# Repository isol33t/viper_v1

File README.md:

# Duck Viper v1 PCB

This repository contains KiCad files for an attempt at the Duck Viper v1 PCB design.

- Work In Progress
- Optional Split Shifts, Split Backspace, Stepped Caps Lock & ISO Enter
- No LEDs
- With 5 rows and 14 columns, there is only 1 pin left on the Atmega

## Files Included
- KiCad project files
- Schematic
- PCB layout

## Usage
Open the project in KiCad to view and modify the design.

## Revision 5.2025

## Thanks yo
- https://github.com/ruiqimao/keyboard-pcb-guide
- https://wiki.ai03.com/books/pcb-design
- https://github.com/evyd13/plain60-b
- https://github.com/evyd13/plain60-c
- https://www.masterzen.fr/2020/05/03/designing-a-keyboard-part-1/
- https://imgur.com/LQXco3J

## Todo
- Leds?
- https://github.com/adamws/keyboard-tools
- https://keyboard-tools.xyz

## Notes
- Is the reset switch position correct?
- [Japanese duplex matrix](https://kbd.news/The-Japanese-duplex-matrix-1391.html)
- [Pulldown resistor on KMAC Happy](https://geekhack.org/index.php?topic=87703.msg2485259#msg2485259)
- [Nexperia 74HC237 3-to-8 line decoder, demultiplexer with address latches](https://assets.nexperia.com/documents/data-sheet/74HC237.pdf)
- [hasu re: 74HC238](https://geekhack.org/index.php?topic=35065.msg966423#msg966423)

## License
MIT License

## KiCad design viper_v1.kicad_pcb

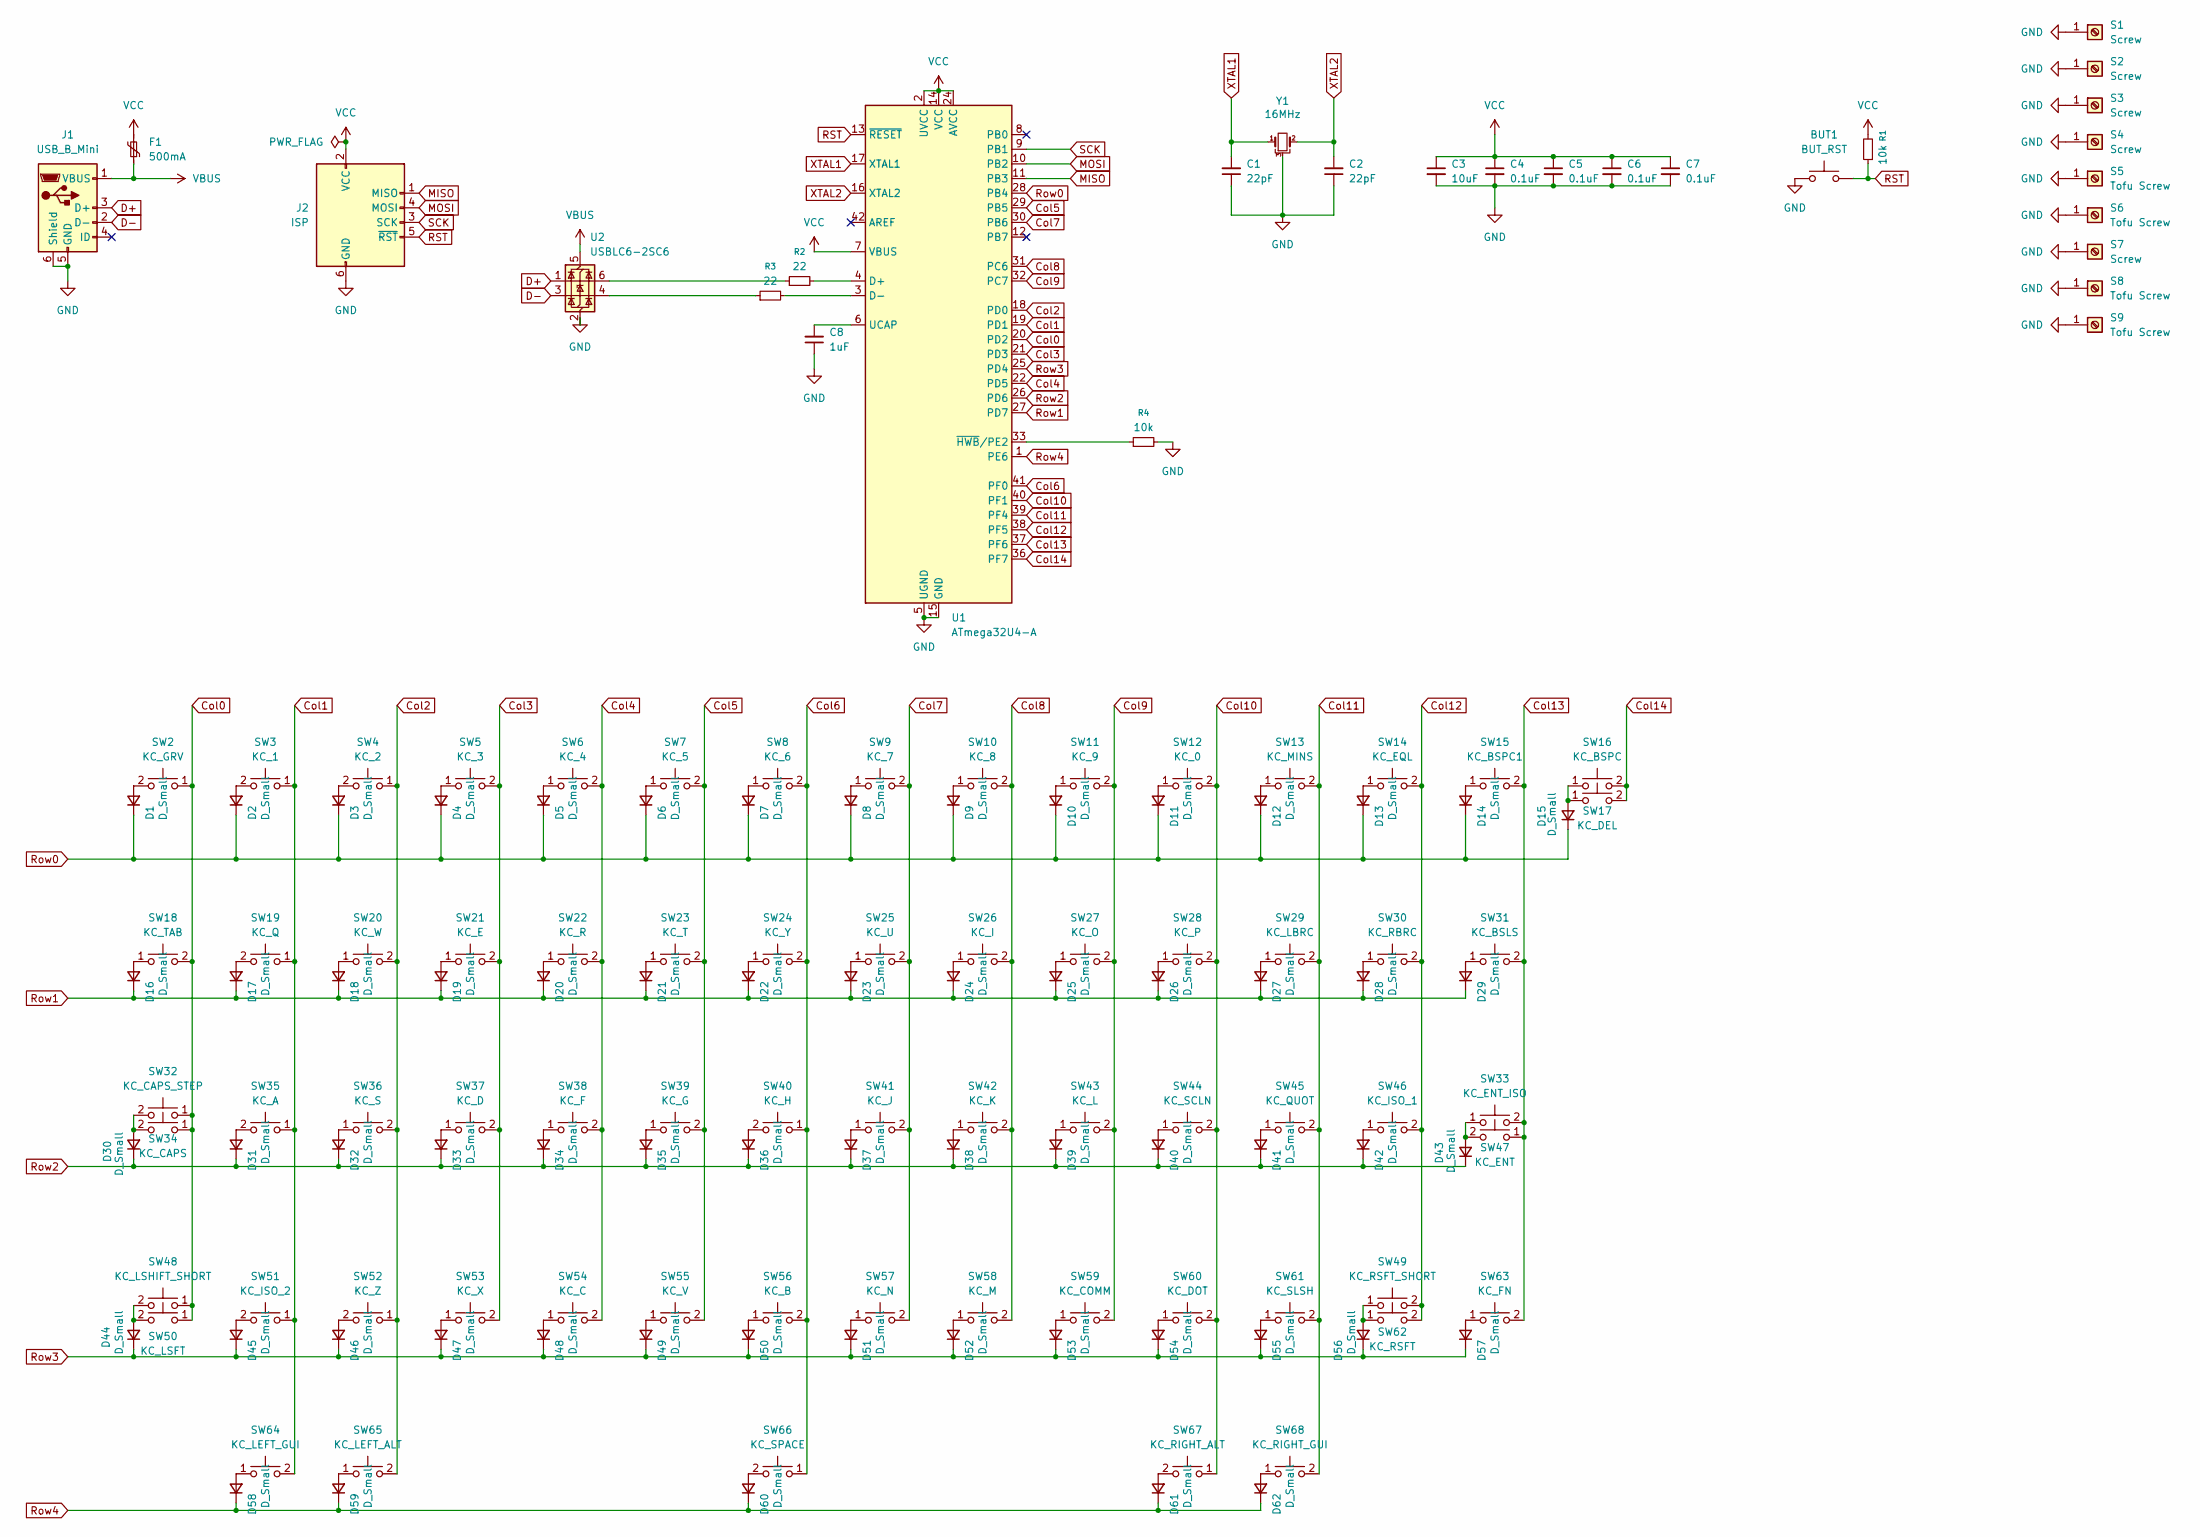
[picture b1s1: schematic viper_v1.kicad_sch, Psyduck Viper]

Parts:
BUT1: BUT_RST; SW_SPST_TL3342
C1, C2: 22pF; C_0805_2012Metric
C3: 10uF; C_0805_2012Metric
C4, C5, C6, C7: 0.1uF; C_0805_2012Metric
C8: 1uF; C_0805_2012Metric
D1, D2, D3, D4, D5, D6, D7, D8, D9, D10, D11, D12, D13, D14, D15, D16, D17, D18, D19, D20, D21, D22, D23, D24, D25, D26, D27, D28, D29, D30, D31, D32, D33, D34, D35, D36, D37, D38, D39, D40, D41, D42, D43, D44, D45, D46, D47, D48, D49, D50, D51, D52, D53, D54, D55, D56, D57, D58, D59, D60, D61, D62: D_Small; D_0805_2012Metric
F1: 500mA; Fuse_0805_2012Metric
J1: USB_B_Mini; HRO-U-M-M5DD-W-1
J2: ISP; isp_standard
R1, R4: 10k; R_0805_2012Metric
R2, R3: 22; R_0805_2012Metric
S1, S2, S3, S4, S7: Screw; 5.5_5x2.5mm
S5, S6, S8, S9: Tofu Screw; 10x5_7x2.5mm
SW2: KC_GRV; MX-Solderable-1U
SW3: KC_1; MX-Solderable-1U
SW4: KC_2; MX-Solderable-1U
SW5: KC_3; MX-Solderable-1U
SW6: KC_4; MX-Solderable-1U
SW7: KC_5; MX-Solderable-1U
SW8: KC_6; MX-Solderable-1U
SW9: KC_7; MX-Solderable-1U
SW10: KC_8; MX-Solderable-1U
SW11: KC_9; MX-Solderable-1U
SW12: KC_0; MX-Solderable-1U
SW13: KC_MINS; MX-Solderable-1U
SW14: KC_EQL; MX-Solderable-1U
SW15: KC_BSPC1; MX-Solderable-1U
SW16: KC_BSPC; MX-Solderable-2U
SW17: KC_DEL; MX-Solderable-1U
SW18: KC_TAB; MX-Solderable-1.5U
SW19: KC_Q; MX-Solderable-1U
SW20: KC_W; MX-Solderable-1U
SW21: KC_E; MX-Solderable-1U
SW22: KC_R; MX-Solderable-1U
SW23: KC_T; MX-Solderable-1U
SW24: KC_Y; MX-Solderable-1U
SW25: KC_U; MX-Solderable-1U
SW26: KC_I; MX-Solderable-1U
SW27: KC_O; MX-Solderable-1U
SW28: KC_P; MX-Solderable-1U
SW29: KC_LBRC; MX-Solderable-1U
SW30: KC_RBRC; MX-Solderable-1U
SW31: KC_BSLS; MX-Solderable-1.5U
SW32: KC_CAPS_STEP; MX-Solderable-1.25U
SW33: KC_ENT_ISO; MX-Solderable-2U-Vertical
SW34: KC_CAPS; MX-Solderable-1.75U
SW35: KC_A; MX-Solderable-1U
SW36: KC_S; MX-Solderable-1U
SW37: KC_D; MX-Solderable-1U
SW38: KC_F; MX-Solderable-1U
SW39: KC_G; MX-Solderable-1U
SW40: KC_H; MX-Solderable-1U
SW41: KC_J; MX-Solderable-1U
SW42: KC_K; MX-Solderable-1U
SW43: KC_L; MX-Solderable-1U
SW44: KC_SCLN; MX-Solderable-1U
SW45: KC_QUOT; MX-Solderable-1U
SW46: KC_ISO_1; MX-Solderable-1U
SW47: KC_ENT; MX-Solderable-2.25U-ReversedStabilizers
SW48: KC_LSHIFT_SHORT; MX-Solderable-1.25U
SW49: KC_RSFT_SHORT; MX-Solderable-1.75U
SW50: KC_LSFT; MX-Solderable-2.25U-ReversedStabilizers
SW51: KC_ISO_2; MX-Solderable-1U
SW52: KC_Z; MX-Solderable-1U
SW53: KC_X; MX-Solderable-1U
SW54: KC_C; MX-Solderable-1U
SW55: KC_V; MX-Solderable-1U
SW56: KC_B; MX-Solderable-1U
SW57: KC_N; MX-Solderable-1U
SW58: KC_M; MX-Solderable-1U
SW59: KC_COMM; MX-Solderable-1U
SW60: KC_DOT; MX-Solderable-1U
SW61: KC_SLSH; MX-Solderable-1U
SW62: KC_RSFT; MX-Solderable-2.75U-ReversedStabilizers
SW63: KC_FN; MX-Solderable-1U
SW64: KC_LEFT_GUI; MX-Solderable-1U
SW65: KC_LEFT_ALT; MX-Solderable-1.5U
SW66: KC_SPACE; MX-Solderable-7U-ReversedStabilizers
SW67: KC_RIGHT_ALT; MX-Solderable-1.5U
SW68: KC_RIGHT_GUI; MX-Solderable-1U
U1: ATmega32U4-A; TQFP-44_10x10mm_P0.8mm
U2: USBLC6-2SC6; SOT-23-6
Y1: 16MHz; crystal_FA238-TSX3225

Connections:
Col0: SW2.1, SW18.2, SW32.1, SW34.1, SW48.1, SW50.1, U1.20 (PD2)
Col1: SW3.1, SW19.1, SW35.1, SW51.1, SW64.2, U1.19 (PD1)
Col2: SW4.1, SW20.2, SW36.2, SW52.1, SW65.2, U1.18 (PD0)
Col3: SW5.2, SW21.2, SW37.2, SW53.2, U1.21 (PD3)
Col4: SW6.2, SW22.2, SW38.2, SW54.2, U1.22 (PD5)
Col5: SW7.2, SW23.2, SW39.2, SW55.2, U1.29 (PB5)
Col6: SW8.2, SW24.2, SW40.1, SW56.2, SW66.1, U1.41 (PF0)
Col7: SW9.2, SW25.2, SW41.2, SW57.2, U1.30 (PB6)
Col8: SW10.2, SW26.2, SW42.2, SW58.2, U1.31 (PC6)
Col9: SW11.2, SW27.2, SW43.2, SW59.2, U1.32 (PC7)
Col10: SW12.2, SW28.2, SW44.2, SW60.2, SW67.1, U1.40 (PF1)
Col11: SW13.2, SW29.2, SW45.2, SW61.2, SW68.2, U1.39 (PF4)
Col12: SW14.2, SW30.2, SW46.2, SW49.2, SW62.2, U1.38 (PF5)
Col13: SW15.2, SW31.2, SW33.2, SW47.1, SW63.2, U1.37 (PF6)
Col14: SW16.2, SW17.2, U1.36 (PF7)
D+: J1.3 (D+), U2.1 (I/O1)
D-: J1.2 (D-), U2.3 (I/O2)
GND: BUT1.1, C1.1, C2.1, C3.2, C4.2, C5.2, C6.2, C7.2, C8.1, J1.5 (GND), J1.6 (Shield), J2.6 (GND), R4.2, S1.1, S2.1, S3.1, S4.1, S5.1, S6.1, S7.1, S8.1, S9.1, U1.5 (UGND), U1.15 (GND), U1.23 (GND), U1.35 (GND), U1.43 (GND), U2.2 (GND), Y1.3
MISO: J2.1 (MISO), U1.11 (PB3)
MOSI: J2.4 (MOSI), U1.10 (PB2)
unnamed: D1.2 (A), SW2.2
unnamed: D2.2 (A), SW3.2
unnamed: D3.2 (A), SW4.2
unnamed: D4.2 (A), SW5.1
unnamed: D5.2 (A), SW6.1
unnamed: D6.2 (A), SW7.1
unnamed: D7.2 (A), SW8.1
unnamed: D8.2 (A), SW9.1
unnamed: D9.2 (A), SW10.1
unnamed: D10.2 (A), SW11.1
unnamed: D11.2 (A), SW12.1
unnamed: D12.2 (A), SW13.1
unnamed: D13.2 (A), SW14.1
unnamed: D14.2 (A), SW15.1
unnamed: D15.2 (A), SW16.1, SW17.1
unnamed: D16.2 (A), SW18.1
unnamed: D17.2 (A), SW19.2
unnamed: D18.2 (A), SW20.1
unnamed: D19.2 (A), SW21.1
unnamed: D20.2 (A), SW22.1
unnamed: D21.2 (A), SW23.1
unnamed: D22.2 (A), SW24.1
unnamed: D23.2 (A), SW25.1
unnamed: D24.2 (A), SW26.1
unnamed: D25.2 (A), SW27.1
unnamed: D26.2 (A), SW28.1
unnamed: D27.2 (A), SW29.1
unnamed: D28.2 (A), SW30.1
unnamed: D29.2 (A), SW31.1
unnamed: D30.2 (A), SW32.2, SW34.2
unnamed: D31.2 (A), SW35.2
unnamed: D32.2 (A), SW36.1
unnamed: D33.2 (A), SW37.1
unnamed: D34.2 (A), SW38.1
unnamed: D35.2 (A), SW39.1
unnamed: D36.2 (A), SW40.2
unnamed: D37.2 (A), SW41.1
unnamed: D38.2 (A), SW42.1
unnamed: D39.2 (A), SW43.1
unnamed: D40.2 (A), SW44.1
unnamed: D41.2 (A), SW45.1
unnamed: D42.2 (A), SW46.1
unnamed: D43.2 (A), SW33.1, SW47.2
unnamed: D44.2 (A), SW48.2, SW50.2
unnamed: D45.2 (A), SW51.2
unnamed: D46.2 (A), SW52.2
unnamed: D47.2 (A), SW53.1
unnamed: D48.2 (A), SW54.1
unnamed: D49.2 (A), SW55.1
unnamed: D50.2 (A), SW56.1
unnamed: D51.2 (A), SW57.1
unnamed: D52.2 (A), SW58.1
unnamed: D53.2 (A), SW59.1
unnamed: D54.2 (A), SW60.1
unnamed: D55.2 (A), SW61.1
unnamed: D56.2 (A), SW49.1, SW62.1
unnamed: D57.2 (A), SW63.1
unnamed: D58.2 (A), SW64.1
unnamed: D59.2 (A), SW65.1
unnamed: D60.2 (A), SW66.2
unnamed: D61.2 (A), SW67.2
unnamed: D62.2 (A), SW68.1
unnamed: R2.1, U2.6 (I/O1)
unnamed: R3.1, U2.4 (I/O2)
unnamed: R2.2, U1.4 (D+)
unnamed: R3.2, U1.3 (D-)
unnamed: C8.2, U1.6 (UCAP)
unnamed: R4.1, U1.33 (~HWB/PE2)
RST: BUT1.2, J2.5 (~RST), R1.1, U1.13 (~RESET)
Row0: D1.1 (K), D2.1 (K), D3.1 (K), D4.1 (K), D5.1 (K), D6.1 (K), D7.1 (K), D8.1 (K), D9.1 (K), D10.1 (K), D11.1 (K), D12.1 (K), D13.1 (K), D14.1 (K), D15.1 (K), U1.28 (PB4)
Row1: D16.1 (K), D17.1 (K), D18.1 (K), D19.1 (K), D20.1 (K), D21.1 (K), D22.1 (K), D23.1 (K), D24.1 (K), D25.1 (K), D26.1 (K), D27.1 (K), D28.1 (K), D29.1 (K), U1.27 (PD7)
Row2: D30.1 (K), D31.1 (K), D32.1 (K), D33.1 (K), D34.1 (K), D35.1 (K), D36.1 (K), D37.1 (K), D38.1 (K), D39.1 (K), D40.1 (K), D41.1 (K), D42.1 (K), D43.1 (K), U1.26 (PD6)
Row3: D44.1 (K), D45.1 (K), D46.1 (K), D47.1 (K), D48.1 (K), D49.1 (K), D50.1 (K), D51.1 (K), D52.1 (K), D53.1 (K), D54.1 (K), D55.1 (K), D56.1 (K), D57.1 (K), U1.25 (PD4)
Row4: D58.1 (K), D59.1 (K), D60.1 (K), D61.1 (K), D62.1 (K), U1.1 (PE6)
SCK: J2.3 (SCK), U1.9 (PB1)
VBUS: F1.1, J1.1 (VBUS), U2.5 (VBUS)
VCC: C3.1, C4.1, C5.1, C6.1, C7.1, F1.2, J2.2 (VCC), R1.2, U1.2 (UVCC), U1.7 (VBUS), U1.14 (VCC), U1.24 (AVCC), U1.34 (VCC), U1.44 (AVCC)
XTAL1: C1.2, U1.17 (XTAL1), Y1.1
XTAL2: C2.2, U1.16 (XTAL2), Y1.2

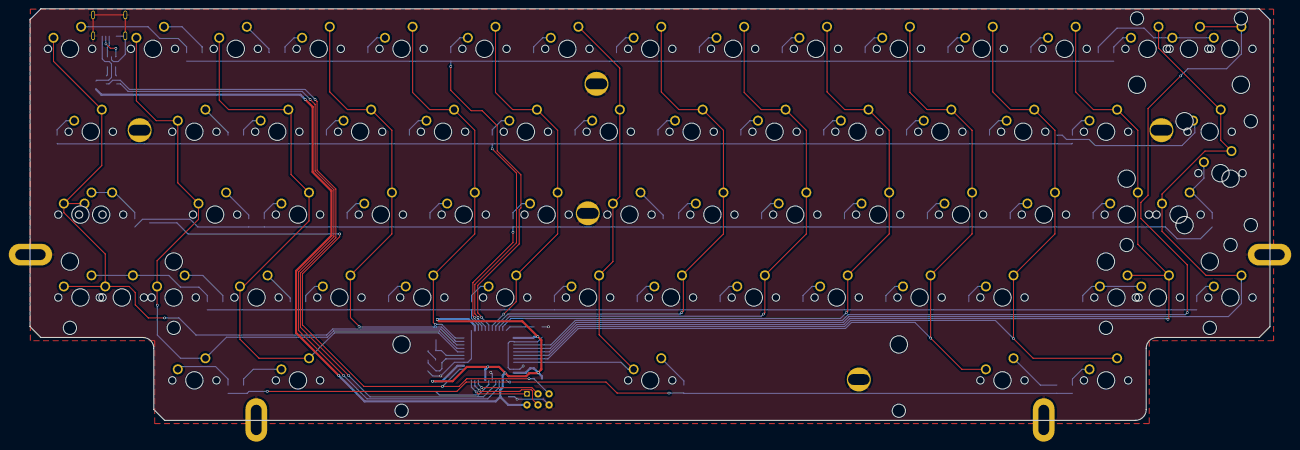
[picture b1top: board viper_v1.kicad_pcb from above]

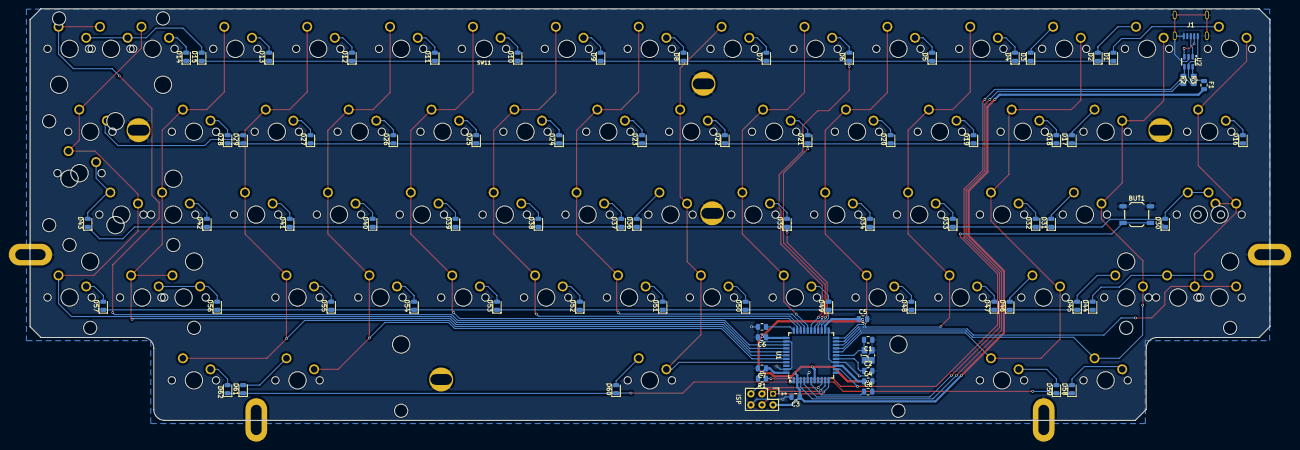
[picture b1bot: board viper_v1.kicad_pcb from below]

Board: 2 copper layers, 285.0 x 94.6 mm, 157 parts (81 on the bottom side), 99 nets.

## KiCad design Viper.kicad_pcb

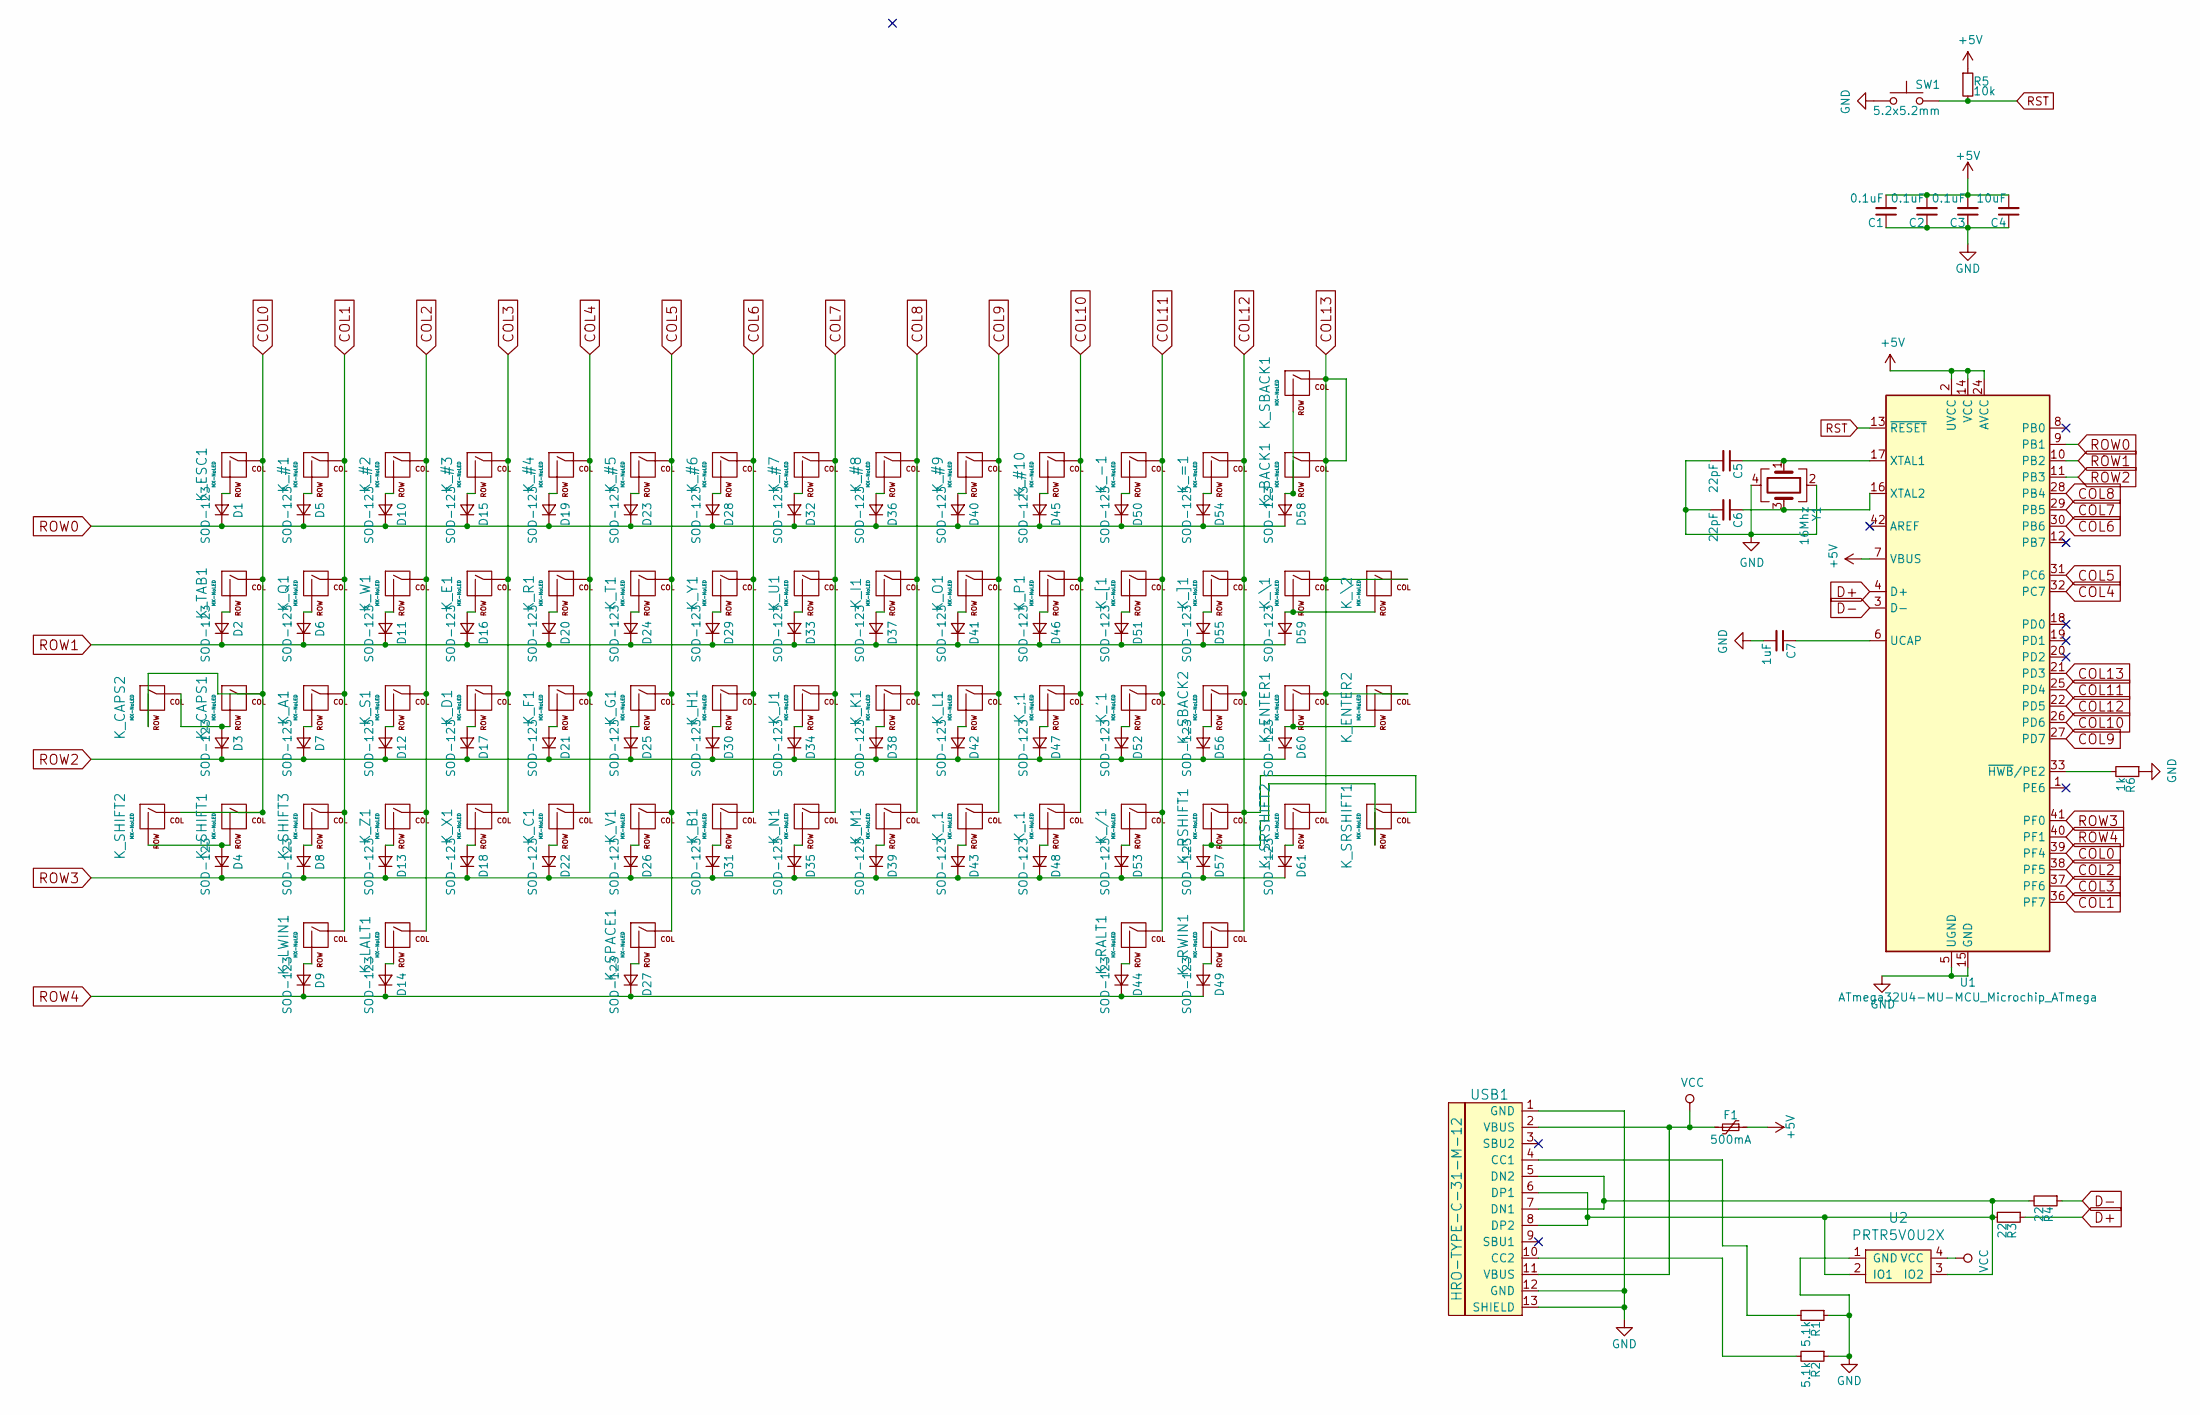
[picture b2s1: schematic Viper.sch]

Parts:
C1, C2, C3: 0.1uF; C_0603_1608Metric
C4: 10uF; C_0603_1608Metric
C5, C6: 22pF; C_0603_1608Metric
C7: 1uF; C_0603_1608Metric
D1, D2, D3, D4, D5, D6, D7, D8, D9, D10, D11, D12, D13, D14, D15, D16, D17, D18, D19, D20, D21, D22, D23, D24, D25, D26, D27, D28, D29, D30, D31, D32, D33, D34, D35, D36, D37, D38, D39, D40, D41, D42, D43, D44, D45, D46, D47, D48, D49, D50, D51, D52, D53, D54, D55, D56, D57, D58, D59, D60, D61: SOD-123; D_SOD-123
F1: 500mA; Fuse_1206_3216Metric
K_#1, K_#2, K_#3, K_#4, K_#5, K_#6, K_#7, K_#8, K_#9, K_#10: MX-NoLED; MX-1U-NoLED
K_'1: MX-NoLED; MX-1U-NoLED
K_,1: MX-NoLED; MX-1U-NoLED
K_-1: MX-NoLED; MX-1U-NoLED
K_.1: MX-NoLED; MX-1U-NoLED
K_/1: MX-NoLED; MX-1U-NoLED
K_;1: MX-NoLED; MX-1U-NoLED
K_=1: MX-NoLED; MX-1U-NoLED
K_A1: MX-NoLED; MX-1U-NoLED
K_B1: MX-NoLED; MX-1U-NoLED
K_BACK1: MX-NoLED; MX-2U-NoLED
K_C1: MX-NoLED; MX-1U-NoLED
K_CAPS1: MX-NoLED; MX-1.75U-NoLED
K_CAPS2: MX-NoLED; MX-1.25U-NoLED
K_D1: MX-NoLED; MX-1U-NoLED
K_E1: MX-NoLED; MX-1U-NoLED
K_ENTER1: MX-NoLED; MX-2.25U-NoLED
K_ENTER2: MX-NoLED; MX-ISO-ReversedStabilizers-NoLED
K_ESC1: MX-NoLED; MX-1U-NoLED
K_F1: MX-NoLED; MX-1U-NoLED
K_G1: MX-NoLED; MX-1U-NoLED
K_H1: MX-NoLED; MX-1U-NoLED
K_I1: MX-NoLED; MX-1U-NoLED
K_J1: MX-NoLED; MX-1U-NoLED
K_K1: MX-NoLED; MX-1U-NoLED
K_L1: MX-NoLED; MX-1U-NoLED
K_LALT1: MX-NoLED; MX-1.5U-NoLED
K_LWIN1: MX-NoLED; MX-1U-NoLED
K_M1: MX-NoLED; MX-1U-NoLED
K_N1: MX-NoLED; MX-1U-NoLED
K_O1: MX-NoLED; MX-1U-NoLED
K_P1: MX-NoLED; MX-1U-NoLED
K_Q1: MX-NoLED; MX-1U-NoLED
K_R1: MX-NoLED; MX-1U-NoLED
K_RALT1: MX-NoLED; MX-1.5U-NoLED
K_RSHIFT1: MX-NoLED; MXOnly-2.25U-NoLED-FLIPPED
K_RWIN1: MX-NoLED; MX-1U-NoLED
K_S1: MX-NoLED; MX-1U-NoLED
K_SBACK1, K_SBACK2: MX-NoLED; MX-1U-NoLED
K_SHIFT1: MX-NoLED; MXOnly-2.25U-NoLED-FLIPPED
K_SHIFT2: MX-NoLED; MX-1.25U-NoLED
K_SHIFT3: MX-NoLED; MX-1U-NoLED
K_SPACE1: MX-NoLED; MX-7U-ReversedStabilizers-NoLED
K_SRSHIFT1: MX-NoLED; MX-1.75U-NoLED
K_SRSHIFT2: MX-NoLED; MX-1U-NoLED
K_T1: MX-NoLED; MX-1U-NoLED
K_TAB1: MX-NoLED; MX-1.5U-NoLED
K_U1: MX-NoLED; MX-1U-NoLED
K_V1: MX-NoLED; MX-1U-NoLED
K_W1: MX-NoLED; MX-1U-NoLED
K_X1: MX-NoLED; MX-1U-NoLED
K_Y1: MX-NoLED; MX-1U-NoLED
K_Z1: MX-NoLED; MX-1U-NoLED
K_[1: MX-NoLED; MX-1U-NoLED
K_\1: MX-NoLED; MX-1.5U-NoLED
K_\2: MX-NoLED; MX-1U-NoLED
K_]1: MX-NoLED; MX-1U-NoLED
R1, R2: 5.1k; R_0805_2012Metric
R3, R4: 22; R_0805_2012Metric
R5: 10k; R_0805_2012Metric
R6: 1k; R_0805_2012Metric
SW1: 5.2x5.2mm; SKQG-1155865
U1: ATmega32U4-MU-MCU_Microchip_ATmega; QFN-44-1EP_7x7mm_Pitch0.5mm
U2: PRTR5V0U2X; SOT143B
USB1: HRO-TYPE-C-31-M-12; HRO-TYPE-C-31-M-12-Assembly
Y1: 16Mhz; Crystal_SMD_3225-4Pin_3.2x2.5mm

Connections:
+5V: C1.2, C2.2, C3.2, C4.2, F1.1, R5.1, U1.2 (UVCC), U1.7 (VBUS), U1.14 (VCC), U1.24 (AVCC), U1.34 (VCC), U1.44 (AVCC)
COL0: K_CAPS1.1 (COL), K_CAPS2.2 (ROW), K_ESC1.1 (COL), K_SHIFT1.1 (COL), K_SHIFT2.1 (COL), K_TAB1.1 (COL), U1.39 (PF4)
COL1: K_#1.1 (COL), K_A1.1 (COL), K_LWIN1.1 (COL), K_Q1.1 (COL), K_SHIFT3.1 (COL), U1.36 (PF7)
COL2: K_#2.1 (COL), K_LALT1.1 (COL), K_S1.1 (COL), K_W1.1 (COL), K_Z1.1 (COL), U1.38 (PF5)
COL3: K_#3.1 (COL), K_D1.1 (COL), K_E1.1 (COL), K_X1.1 (COL), U1.37 (PF6)
COL4: K_#4.1 (COL), K_C1.1 (COL), K_F1.1 (COL), K_R1.1 (COL), U1.32 (PC7)
COL5: K_#5.1 (COL), K_G1.1 (COL), K_SPACE1.1 (COL), K_T1.1 (COL), K_V1.1 (COL), U1.31 (PC6)
COL6: K_#6.1 (COL), K_B1.1 (COL), K_H1.1 (COL), K_Y1.1 (COL), U1.30 (PB6)
COL7: K_#7.1 (COL), K_J1.1 (COL), K_N1.1 (COL), K_U1.1 (COL), U1.29 (PB5)
COL8: K_#8.1 (COL), K_I1.1 (COL), K_K1.1 (COL), K_M1.1 (COL), U1.28 (PB4)
COL9: K_#9.1 (COL), K_,1.1 (COL), K_L1.1 (COL), K_O1.1 (COL), U1.27 (PD7)
COL10: K_#10.1 (COL), K_.1.1 (COL), K_;1.1 (COL), K_P1.1 (COL), U1.26 (PD6)
COL11: K_'1.1 (COL), K_-1.1 (COL), K_/1.1 (COL), K_RALT1.1 (COL), K_[1.1 (COL), U1.25 (PD4)
COL12: K_=1.1 (COL), K_RSHIFT1.1 (COL), K_RWIN1.1 (COL), K_SBACK2.1 (COL), K_SRSHIFT1.1 (COL), K_]1.1 (COL), U1.22 (PD5)
COL13: K_BACK1.1 (COL), K_ENTER1.1 (COL), K_ENTER2.1 (COL), K_SBACK1.1 (COL), K_SRSHIFT2.1 (COL), K_\1.1 (COL), K_\2.1 (COL), U1.21 (PD3)
D+: R3.1, U1.4 (D+)
D-: R4.1, U1.3 (D-)
GND: C1.1, C2.1, C3.1, C4.1, C5.2, C6.2, C7.2, R1.1, R2.1, R6.1, SW1.1, U1.5 (UGND), U1.15 (GND), U1.23 (GND), U1.35 (GND), U1.43 (GND), U1.45 (GND), U2.1 (GND), USB1.1 (GND), USB1.12 (GND), USB1.13 (SHIELD), Y1.2, Y1.4
unnamed: C5.1, U1.17 (XTAL1), Y1.1
unnamed: C6.1, U1.16 (XTAL2), Y1.3
unnamed: C7.1, U1.6 (UCAP)
unnamed: D1.2 (A), K_ESC1.2 (ROW)
unnamed: D2.2 (A), K_TAB1.2 (ROW)
unnamed: D3.2 (A), K_CAPS1.2 (ROW), K_CAPS2.1 (COL)
unnamed: D4.2 (A), K_SHIFT1.2 (ROW), K_SHIFT2.2 (ROW)
unnamed: D5.2 (A), K_#1.2 (ROW)
unnamed: D6.2 (A), K_Q1.2 (ROW)
unnamed: D7.2 (A), K_A1.2 (ROW)
unnamed: D8.2 (A), K_SHIFT3.2 (ROW)
unnamed: D9.2 (A), K_LWIN1.2 (ROW)
unnamed: D10.2 (A), K_#2.2 (ROW)
unnamed: D11.2 (A), K_W1.2 (ROW)
unnamed: D12.2 (A), K_S1.2 (ROW)
unnamed: D13.2 (A), K_Z1.2 (ROW)
unnamed: D14.2 (A), K_LALT1.2 (ROW)
unnamed: D15.2 (A), K_#3.2 (ROW)
unnamed: D16.2 (A), K_E1.2 (ROW)
unnamed: D17.2 (A), K_D1.2 (ROW)
unnamed: D18.2 (A), K_X1.2 (ROW)
unnamed: D19.2 (A), K_#4.2 (ROW)
unnamed: D20.2 (A), K_R1.2 (ROW)
unnamed: D21.2 (A), K_F1.2 (ROW)
unnamed: D22.2 (A), K_C1.2 (ROW)
unnamed: D23.2 (A), K_#5.2 (ROW)
unnamed: D24.2 (A), K_T1.2 (ROW)
unnamed: D25.2 (A), K_G1.2 (ROW)
unnamed: D26.2 (A), K_V1.2 (ROW)
unnamed: D27.2 (A), K_SPACE1.2 (ROW)
unnamed: D28.2 (A), K_#6.2 (ROW)
unnamed: D29.2 (A), K_Y1.2 (ROW)
unnamed: D30.2 (A), K_H1.2 (ROW)
unnamed: D31.2 (A), K_B1.2 (ROW)
unnamed: D32.2 (A), K_#7.2 (ROW)
unnamed: D33.2 (A), K_U1.2 (ROW)
unnamed: D34.2 (A), K_J1.2 (ROW)
unnamed: D35.2 (A), K_N1.2 (ROW)
unnamed: D36.2 (A), K_#8.2 (ROW)
unnamed: D37.2 (A), K_I1.2 (ROW)
unnamed: D38.2 (A), K_K1.2 (ROW)
unnamed: D39.2 (A), K_M1.2 (ROW)
unnamed: D40.2 (A), K_#9.2 (ROW)
unnamed: D41.2 (A), K_O1.2 (ROW)
unnamed: D42.2 (A), K_L1.2 (ROW)
unnamed: D43.2 (A), K_,1.2 (ROW)
unnamed: D44.2 (A), K_RALT1.2 (ROW)
unnamed: D45.2 (A), K_#10.2 (ROW)
unnamed: D46.2 (A), K_P1.2 (ROW)
unnamed: D47.2 (A), K_;1.2 (ROW)
unnamed: D48.2 (A), K_.1.2 (ROW)
unnamed: D49.2 (A), K_RWIN1.2 (ROW)
unnamed: D50.2 (A), K_-1.2 (ROW)
unnamed: D51.2 (A), K_[1.2 (ROW)
unnamed: D52.2 (A), K_'1.2 (ROW)
unnamed: D53.2 (A), K_/1.2 (ROW)
unnamed: D54.2 (A), K_=1.2 (ROW)
unnamed: D55.2 (A), K_]1.2 (ROW)
unnamed: D56.2 (A), K_SBACK2.2 (ROW)
unnamed: D57.2 (A), K_RSHIFT1.2 (ROW), K_SRSHIFT1.2 (ROW)
unnamed: D58.2 (A), K_BACK1.2 (ROW), K_SBACK1.2 (ROW)
unnamed: D59.2 (A), K_\1.2 (ROW), K_\2.2 (ROW)
unnamed: D60.2 (A), K_ENTER1.2 (ROW), K_ENTER2.2 (ROW)
unnamed: D61.2 (A), K_SRSHIFT2.2 (ROW)
unnamed: R1.2, USB1.4 (CC1)
unnamed: R2.2, USB1.10 (CC2)
unnamed: R6.2, U1.33 (~HWB~/PE2)
ROW0: D1.1 (K), D5.1 (K), D10.1 (K), D15.1 (K), D19.1 (K), D23.1 (K), D28.1 (K), D32.1 (K), D36.1 (K), D40.1 (K), D45.1 (K), D50.1 (K), D54.1 (K), D58.1 (K), U1.9 (PB1)
ROW1: D2.1 (K), D6.1 (K), D11.1 (K), D16.1 (K), D20.1 (K), D24.1 (K), D29.1 (K), D33.1 (K), D37.1 (K), D41.1 (K), D46.1 (K), D51.1 (K), D55.1 (K), D59.1 (K), U1.10 (PB2)
ROW2: D3.1 (K), D7.1 (K), D12.1 (K), D17.1 (K), D21.1 (K), D25.1 (K), D30.1 (K), D34.1 (K), D38.1 (K), D42.1 (K), D47.1 (K), D52.1 (K), D56.1 (K), D60.1 (K), U1.11 (PB3)
ROW3: D4.1 (K), D8.1 (K), D13.1 (K), D18.1 (K), D22.1 (K), D26.1 (K), D31.1 (K), D35.1 (K), D39.1 (K), D43.1 (K), D48.1 (K), D53.1 (K), D57.1 (K), D61.1 (K), U1.41 (PF0)
ROW4: D9.1 (K), D14.1 (K), D27.1 (K), D44.1 (K), D49.1 (K), U1.40 (PF1)
RST: R5.2, SW1.2, U1.13 (~RESET)
VCC: F1.2, U2.4 (VCC), USB1.2 (VBUS), USB1.11 (VBUS)

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
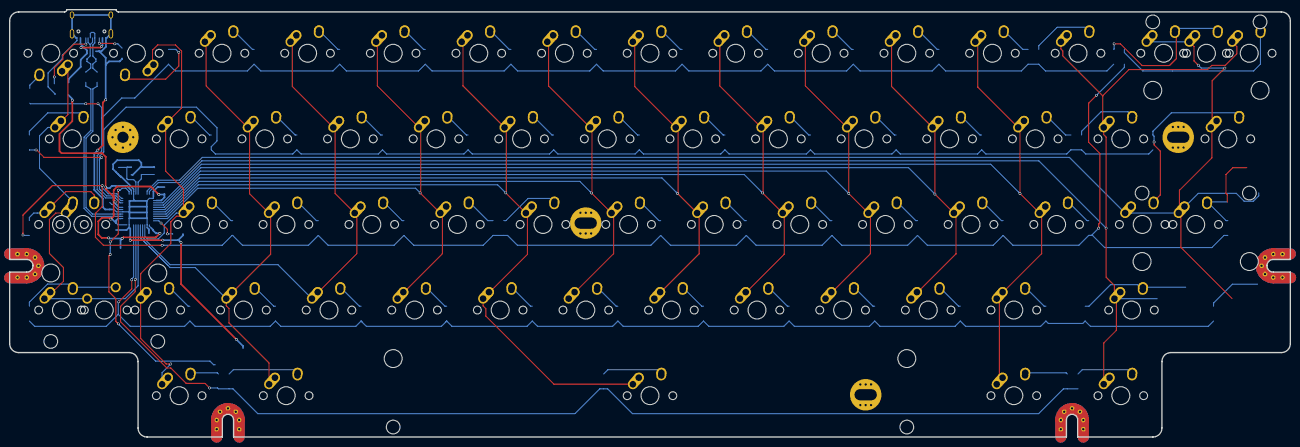
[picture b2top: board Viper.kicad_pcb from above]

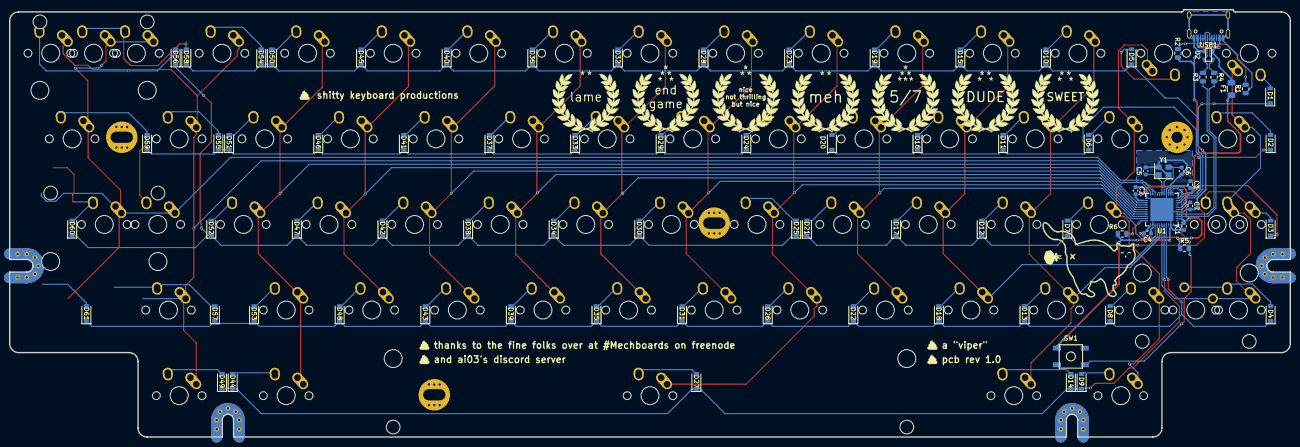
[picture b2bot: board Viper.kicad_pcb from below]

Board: 2 copper layers, 285.0 x 95.1 mm, 188 parts (124 on the bottom side), 93 nets.

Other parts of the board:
X1: G***; X_1
cat_outline20: G***; cat_outline20
cateye2, cateye2#2: G***; cateye2
cateye10, cateye10#2, cateye10#3, cateye10#4, cateye10#5, cateye10#6, cateye10#7: G***; laurels10
catsnout1: G***; catsnout1
fart8: G***; fart8
star1, star1#2, star1#3, star1#4, star1#5, star1#6, star1#7, star1#8, star1#9, star1#10, star1#11, star1#12, star1#13, star1#14, star1#15, star1#16, star1#17, star1#18, star1#19, star1#20, star1#21, star1#22, star1#23, star1#24, star1#25, star1#26: G***; star1
turd2, turd2#2, turd2#3, turd2#4, turd2#5: G***; turd2

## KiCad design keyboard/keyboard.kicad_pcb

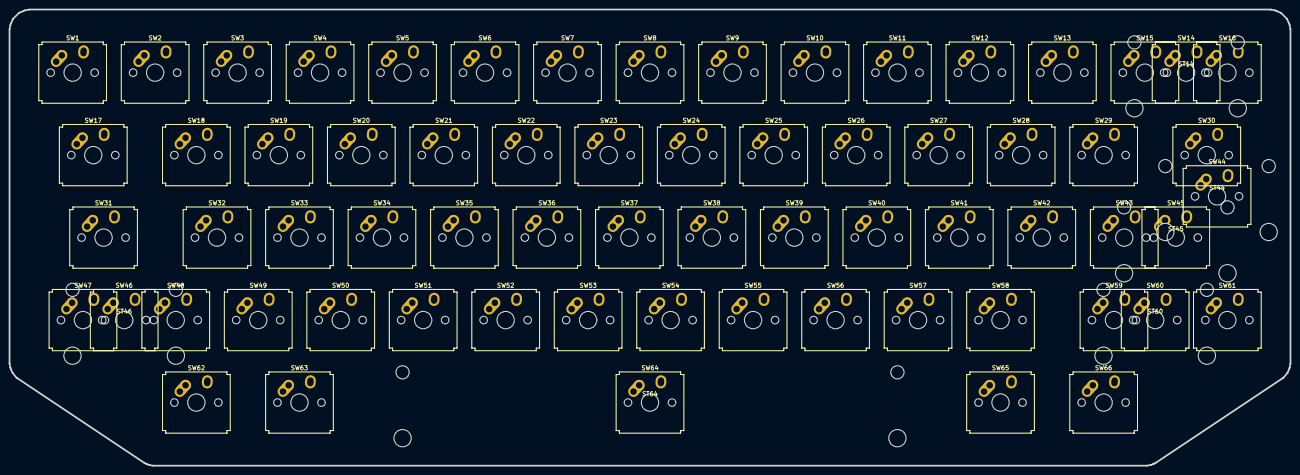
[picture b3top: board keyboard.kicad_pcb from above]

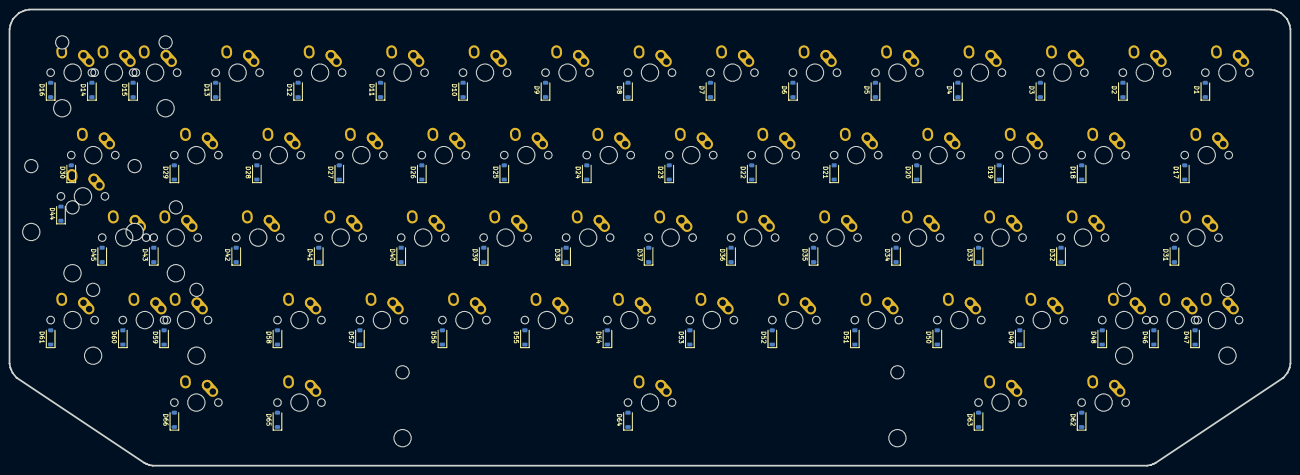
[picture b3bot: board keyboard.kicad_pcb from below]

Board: 2 copper layers, 295.9 x 105.4 mm, 138 parts (66 on the bottom side), 86 nets, no tracks yet.

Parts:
D1, D2, D3, D4, D5, D6, D7, D8, D9, D10, D11, D12, D13, D14, D15, D16, D17, D18, D19, D20, D21, D22, D23, D24, D25, D26, D27, D28, D29, D30, D31, D32, D33, D34, D35, D36, D37, D38, D39, D40, D41, D42, D43, D44, D45, D46, D47, D48, D49, D50, D51, D52, D53, D54, D55, D56, D57, D58, D59, D60, D61, D62, D63, D64, D65, D66: D; D_SOD-123
ST14, ST44, ST45, ST46, ST60: MountingHole; Stabilizer_Cherry_MX_2.00u
ST64: MountingHole; Stabilizer_Cherry_MX_7.00u
SW1, SW2, SW3, SW4, SW5, SW6, SW7, SW8, SW9, SW10, SW11, SW12, SW13, SW15, SW16, SW18, SW19, SW20, SW21, SW22, SW23, SW24, SW25, SW26, SW27, SW28, SW29, SW32, SW33, SW34, SW35, SW36, SW37, SW38, SW39, SW40, SW41, SW42, SW43, SW44, SW48, SW49, SW50, SW51, SW52, SW53, SW54, SW55, SW56, SW57, SW58, SW61, SW62, SW66: SW_Push; SW_Hybrid_Cherry_MX_Alps_1.00u
SW14: SW_Push; SW_Hybrid_Cherry_MX_Alps_2.00u
SW17, SW30, SW63, SW65: SW_Push; SW_Hybrid_Cherry_MX_Alps_1.50u
SW31, SW59: SW_Push; SW_Hybrid_Cherry_MX_Alps_1.75u
SW45, SW46: SW_Push; SW_Hybrid_Cherry_MX_Alps_2.25u
SW47: SW_Push; SW_Hybrid_Cherry_MX_Alps_1.25u
SW60: SW_Push; SW_Hybrid_Cherry_MX_Alps_2.75u
SW64: SW_Push; SW_Hybrid_Cherry_MX_Alps_7.00u

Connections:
COL3: SW1.1, SW17.1, SW31.1, SW46.1, SW47.1
COL4: SW2.1, SW18.1, SW32.1, SW48.1, SW62.1
COL5: SW3.1, SW19.1, SW33.1, SW49.1, SW63.1
COL6: SW4.1, SW20.1, SW34.1, SW50.1
COL7: SW5.1, SW21.1, SW35.1, SW51.1
COL8: SW6.1, SW22.1, SW36.1, SW52.1
COL9: SW7.1, SW23.1, SW37.1, SW53.1
COL10: SW8.1, SW24.1, SW38.1, SW54.1, SW64.1
COL11: SW9.1, SW25.1, SW39.1, SW55.1
COL12: SW10.1, SW26.1, SW40.1, SW56.1
COL13: SW11.1, SW27.1, SW41.1, SW57.1
COL14: SW12.1, SW28.1, SW42.1, SW58.1, SW65.1
COL15: SW13.1, SW29.1, SW43.1, SW59.1, SW66.1
COL16: SW14.1, SW15.1, SW30.1, SW44.1, SW45.1, SW60.1
COL17: SW16.1, SW61.1
unnamed: D1.2, SW1.2
unnamed: D2.2, SW2.2
unnamed: D3.2, SW3.2
unnamed: D4.2, SW4.2
unnamed: D5.2, SW5.2
unnamed: D6.2, SW6.2
unnamed: D7.2, SW7.2
unnamed: D8.2, SW8.2
unnamed: D9.2, SW9.2
unnamed: D10.2, SW10.2
unnamed: D11.2, SW11.2
unnamed: D12.2, SW12.2
unnamed: D13.2, SW13.2
unnamed: D14.2, SW14.2
unnamed: D15.2, SW15.2
unnamed: D16.2, SW16.2
unnamed: D17.2, SW17.2
unnamed: D18.2, SW18.2
unnamed: D19.2, SW19.2
unnamed: D20.2, SW20.2
unnamed: D21.2, SW21.2
unnamed: D22.2, SW22.2
unnamed: D23.2, SW23.2
unnamed: D24.2, SW24.2
unnamed: D25.2, SW25.2
unnamed: D26.2, SW26.2
unnamed: D27.2, SW27.2
unnamed: D28.2, SW28.2
unnamed: D29.2, SW29.2
unnamed: D30.2, SW30.2
unnamed: D31.2, SW31.2
unnamed: D32.2, SW32.2
unnamed: D33.2, SW33.2
unnamed: D34.2, SW34.2
unnamed: D35.2, SW35.2
unnamed: D36.2, SW36.2
unnamed: D37.2, SW37.2
unnamed: D38.2, SW38.2
unnamed: D39.2, SW39.2
unnamed: D40.2, SW40.2
unnamed: D41.2, SW41.2
unnamed: D42.2, SW42.2
unnamed: D43.2, SW43.2
unnamed: D44.2, SW44.2
unnamed: D45.2, SW45.2
unnamed: D46.2, SW46.2
unnamed: D47.2, SW47.2
unnamed: D48.2, SW48.2
unnamed: D49.2, SW49.2
unnamed: D50.2, SW50.2
unnamed: D51.2, SW51.2
unnamed: D52.2, SW52.2
unnamed: D53.2, SW53.2
unnamed: D54.2, SW54.2
unnamed: D55.2, SW55.2
unnamed: D56.2, SW56.2
unnamed: D57.2, SW57.2
unnamed: D58.2, SW58.2
unnamed: D59.2, SW59.2
unnamed: D60.2, SW60.2
unnamed: D61.2, SW61.2
unnamed: D62.2, SW62.2
unnamed: D63.2, SW63.2
unnamed: D64.2, SW64.2
unnamed: D65.2, SW65.2
unnamed: D66.2, SW66.2
ROW0: D1.1, D2.1, D3.1, D4.1, D5.1, D6.1, D7.1, D8.1, D9.1, D10.1, D11.1, D12.1, D13.1, D14.1, D15.1, D16.1
ROW1: D17.1, D18.1, D19.1, D20.1, D21.1, D22.1, D23.1, D24.1, D25.1, D26.1, D27.1, D28.1, D29.1, D30.1
ROW2: D31.1, D32.1, D33.1, D34.1, D35.1, D36.1, D37.1, D38.1, D39.1, D40.1, D41.1, D42.1, D43.1, D44.1, D45.1
ROW3: D46.1, D47.1, D48.1, D49.1, D50.1, D51.1, D52.1, D53.1, D54.1, D55.1, D56.1, D57.1, D58.1, D59.1, D60.1, D61.1
ROW4: D62.1, D63.1, D64.1, D65.1, D66.1

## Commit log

2025-05-05 init
2025-05-05 Add README & LICENSE
2025-05-05 Add jlcpcb production file with gerbers from rev1 and scans.
2025-05-15 Cleanup of old half-baked attempt
    Fresh start
    Included ai03 random-keyboard-parts submodule & set up libs in kicad.
    Add first rows/columns
2025-05-15 Assigned footprints
    Updated/reannotated schematic
    init pcb with viper outline
    Add ISP header
2025-05-15 Added rows/columns for simple wkl layout
    Added values to keys in schematic & updated meta keys
    Aligned switches & diodes
    Moved some footprints around to prevent overlapping.
    Added PWR Flags & connected shield
    Custom SKQG footprint.
    Set up 15mil power netclass for +5V, VCC & GND
2025-05-15 Moved footprints to 0,0
    Added better mounting holes
    Testing different usb miniB footprints & replaced mounting holes.
    Added another decoupling cap.
    Reannotated parts
    Centered diodes under switches where possible
    Changed PCB edges around USB connector & added (optional) rounded corners.
2025-05-15 Placed new footprints for iso enter, short shifts, stepped caps, fn & 2 more iso switches.
    Added USBLC6-2SC6 for ESD protection
2025-05-15 Fixed broken cols for stacked keys & added HRO-U-M-M5DD-W-1.kicad_mod from mymakercorner/Phoenix_Project_No1
    Set wider track width for power & default.
    Moved parts around usb connector around
    Started wiring usb.
    Added GND zones
2025-05-15 Swapped ISP header & xtal footprint & connected all ratsnests
    aligned vias
    Renamed some screws & removed net labels
2025-05-15 Included viper v1 pcb dimensions
2025-05-15 Fixed bottom pcb outline
2025-05-15 Added default 60 measurements on user comment 4, viper measurements on user comment 3
    Moved all parts from 0,0 to 25,25
2025-05-15 Also moved zones to 25,25.
2025-05-15 Created simple footprint of viper v1 edge cuts.
2025-05-16 Replaced edge cuts with viper footprint
    Aligned outline with switch footprints.
2025-05-16 init kle via layout for duck viper v1
